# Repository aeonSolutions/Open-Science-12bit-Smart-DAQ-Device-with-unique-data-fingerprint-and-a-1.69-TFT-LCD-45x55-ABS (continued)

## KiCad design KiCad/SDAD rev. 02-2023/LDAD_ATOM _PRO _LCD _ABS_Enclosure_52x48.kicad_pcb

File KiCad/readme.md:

[PCB-Prototyping-Catalogue](https://github.com/aeonSolutions/PCB-Prototyping-Catalogue)  >>  [Laboratory Automation](https://github.com/aeonSolutions/PCB-Prototyping-Catalogue/tree/main/Laboratory%20Automation)  >>  [Smart DAQ](https://github.com/aeonSolutions/PCB-Prototyping-Catalogue/tree/main/Smart%20DAQ)  >> [12-bit Smart DAQs](https://github.com/aeonSolutions/PCB-Prototyping-Catalogue/tree/main/Smart%20DAQ/12-bit) >> 12-bit Smart DAQ Device with unique data fingerprint and a 1.69" TFT LCD  45x55 ABS

<div align="right">
 <a href="https://github-com.translate.goog/aeonSolutions/Open-Science-12bit-Smart-DAQ-Device-with-unique-data-fingerprint-and-a-1.69-TFT-LCD-45x55-ABS?_x_tr_sl=en&_x_tr_tl=pt&_x_tr_hl=en&_x_tr_pto=wapp">Change language</a>  <br>
Last change 13-04-2024
</div>

<br>

This folder contains the KiCad Project files, for the hardware electronics of the S.D.A.D.  Each KiCad project is available with a [creative commons share alike non-commercial license](https://creativecommons.org/licenses/by-nc-sa/4.0/deed.en) . 

<p align="center">
  <strong> <a href="https://aeonsolutions.github.io/portfolio/hardware_electronics/laboratory/">Interactive web view of the PCB Layout</a> </strong> <br>
 <sup>Click to view the latest revision of the PCB Layout</sup>
</p>

However, they're not fully complete. If you like it and are looking to use it on your projects, you can download the complete Kicad project files with a one-time donation, [click here](https://github.com/sponsors/aeonSolutions) to learn how,  and don't forget to include it in a message the name of the module/hardware electronics you need. <br> Thank you 🙏.

### Support all these open hardware projects and become a GitHub sponsor  
Did you like any of my PCB KiCad Designs? Help and Support my open work to all by becoming a GitHub sponsor.

<p align="center">

</p>

#

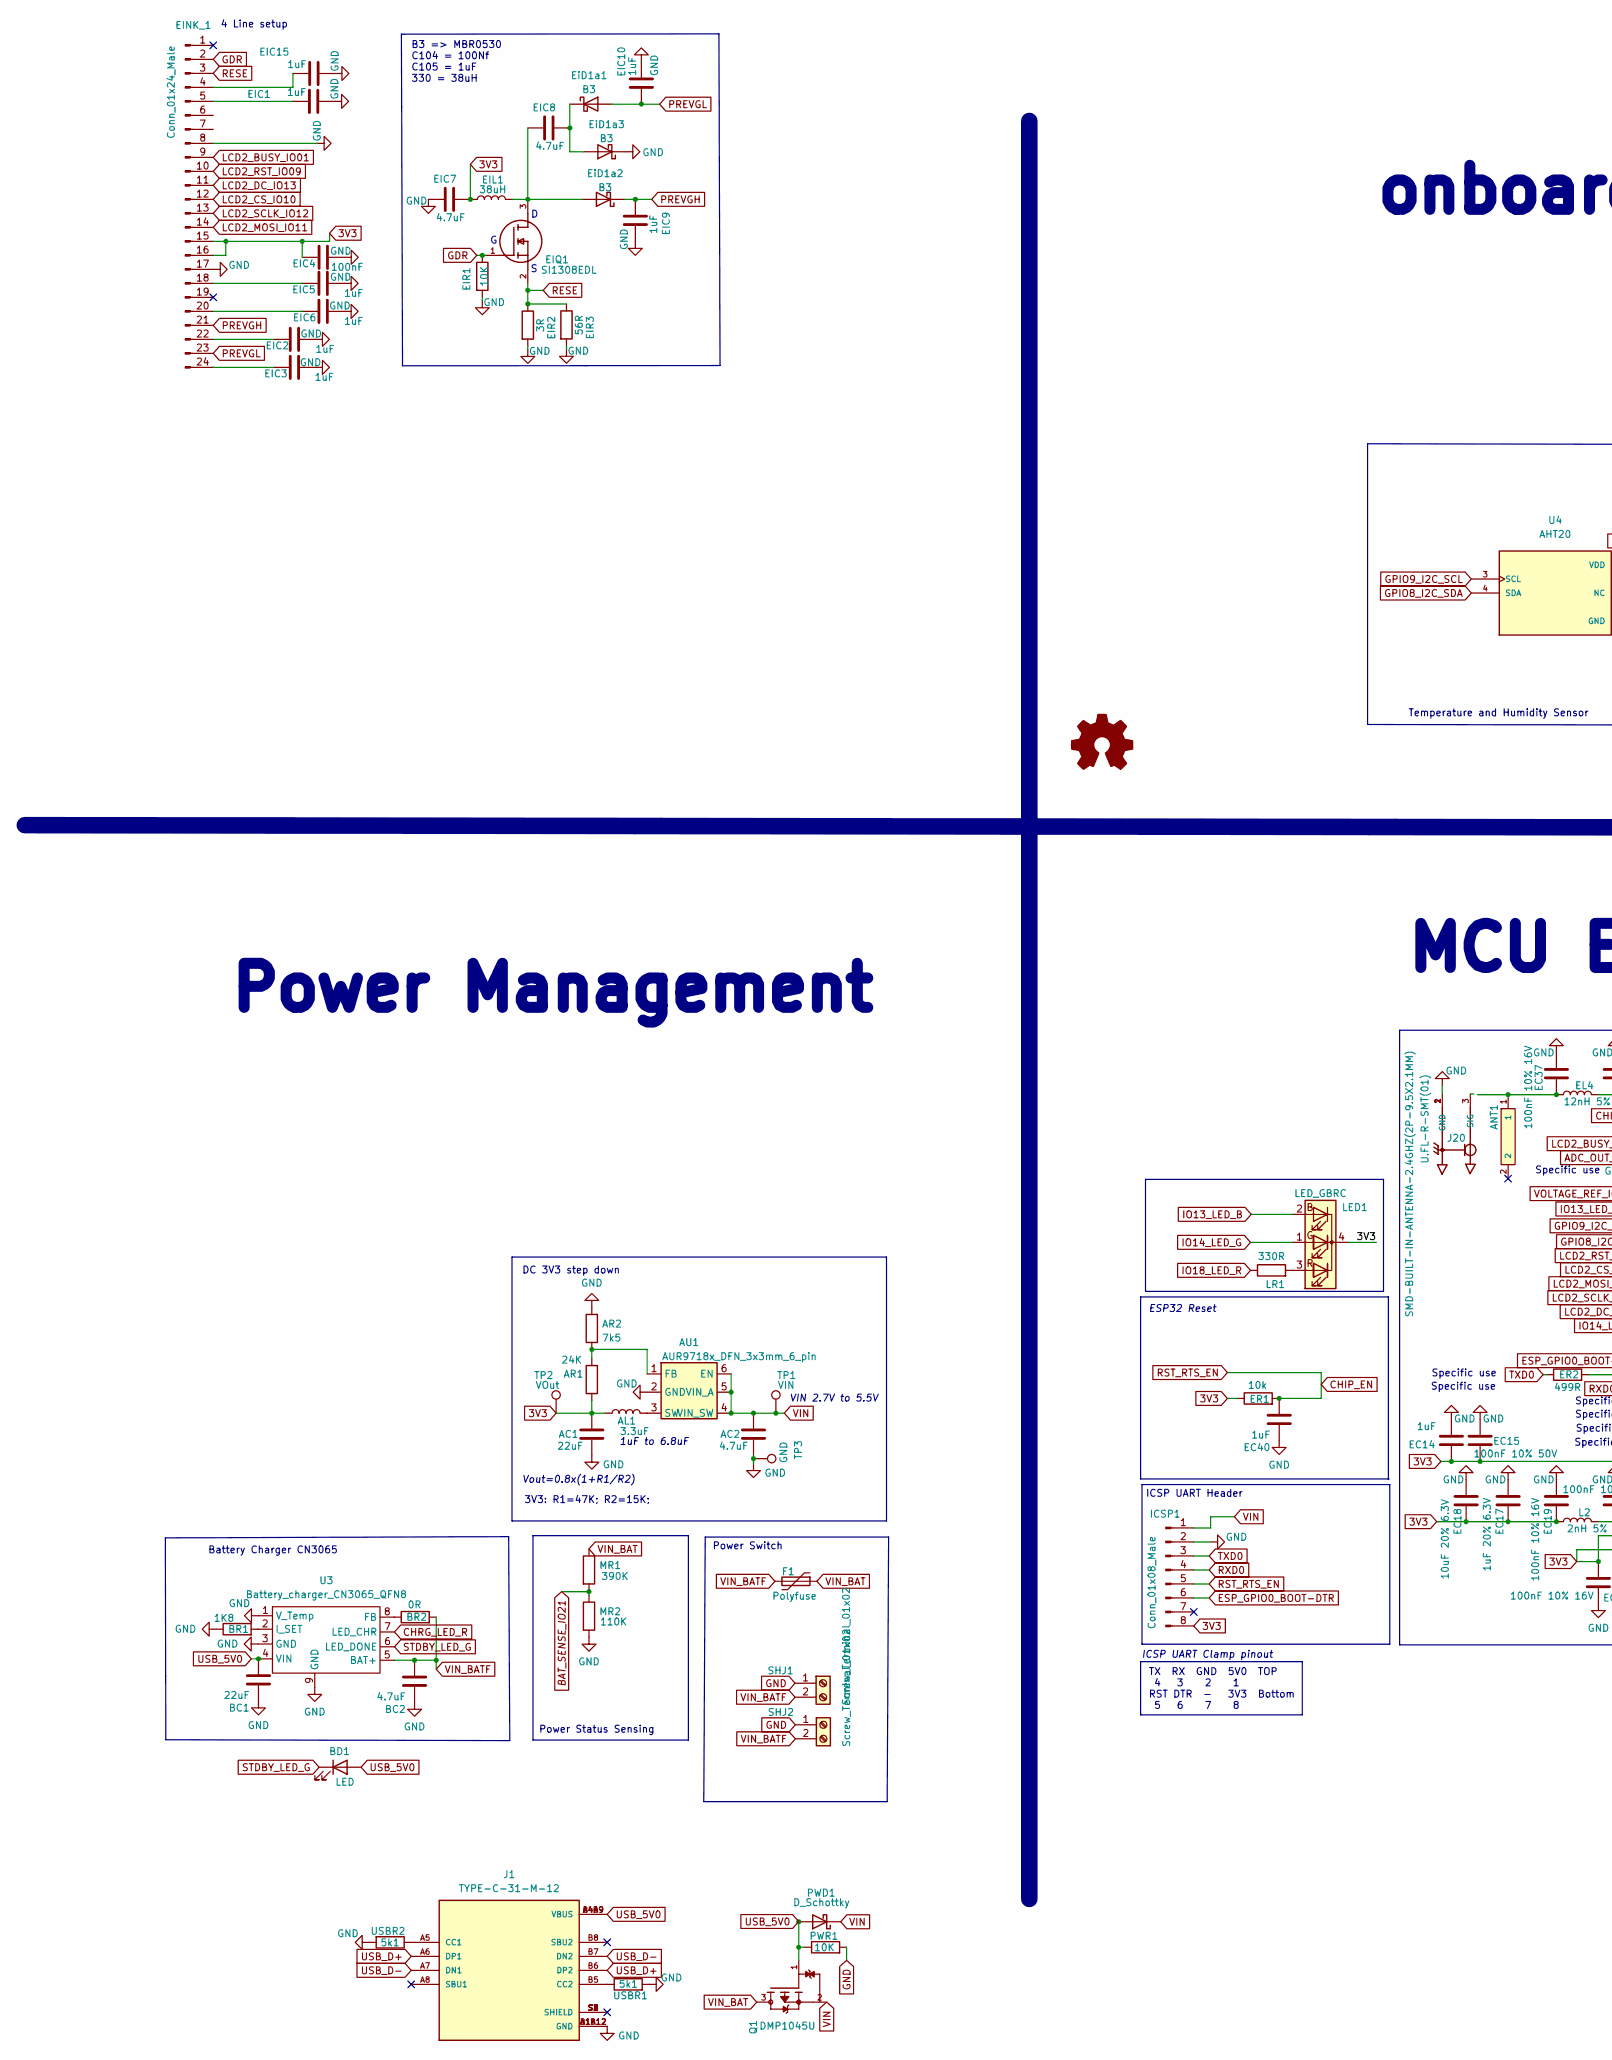
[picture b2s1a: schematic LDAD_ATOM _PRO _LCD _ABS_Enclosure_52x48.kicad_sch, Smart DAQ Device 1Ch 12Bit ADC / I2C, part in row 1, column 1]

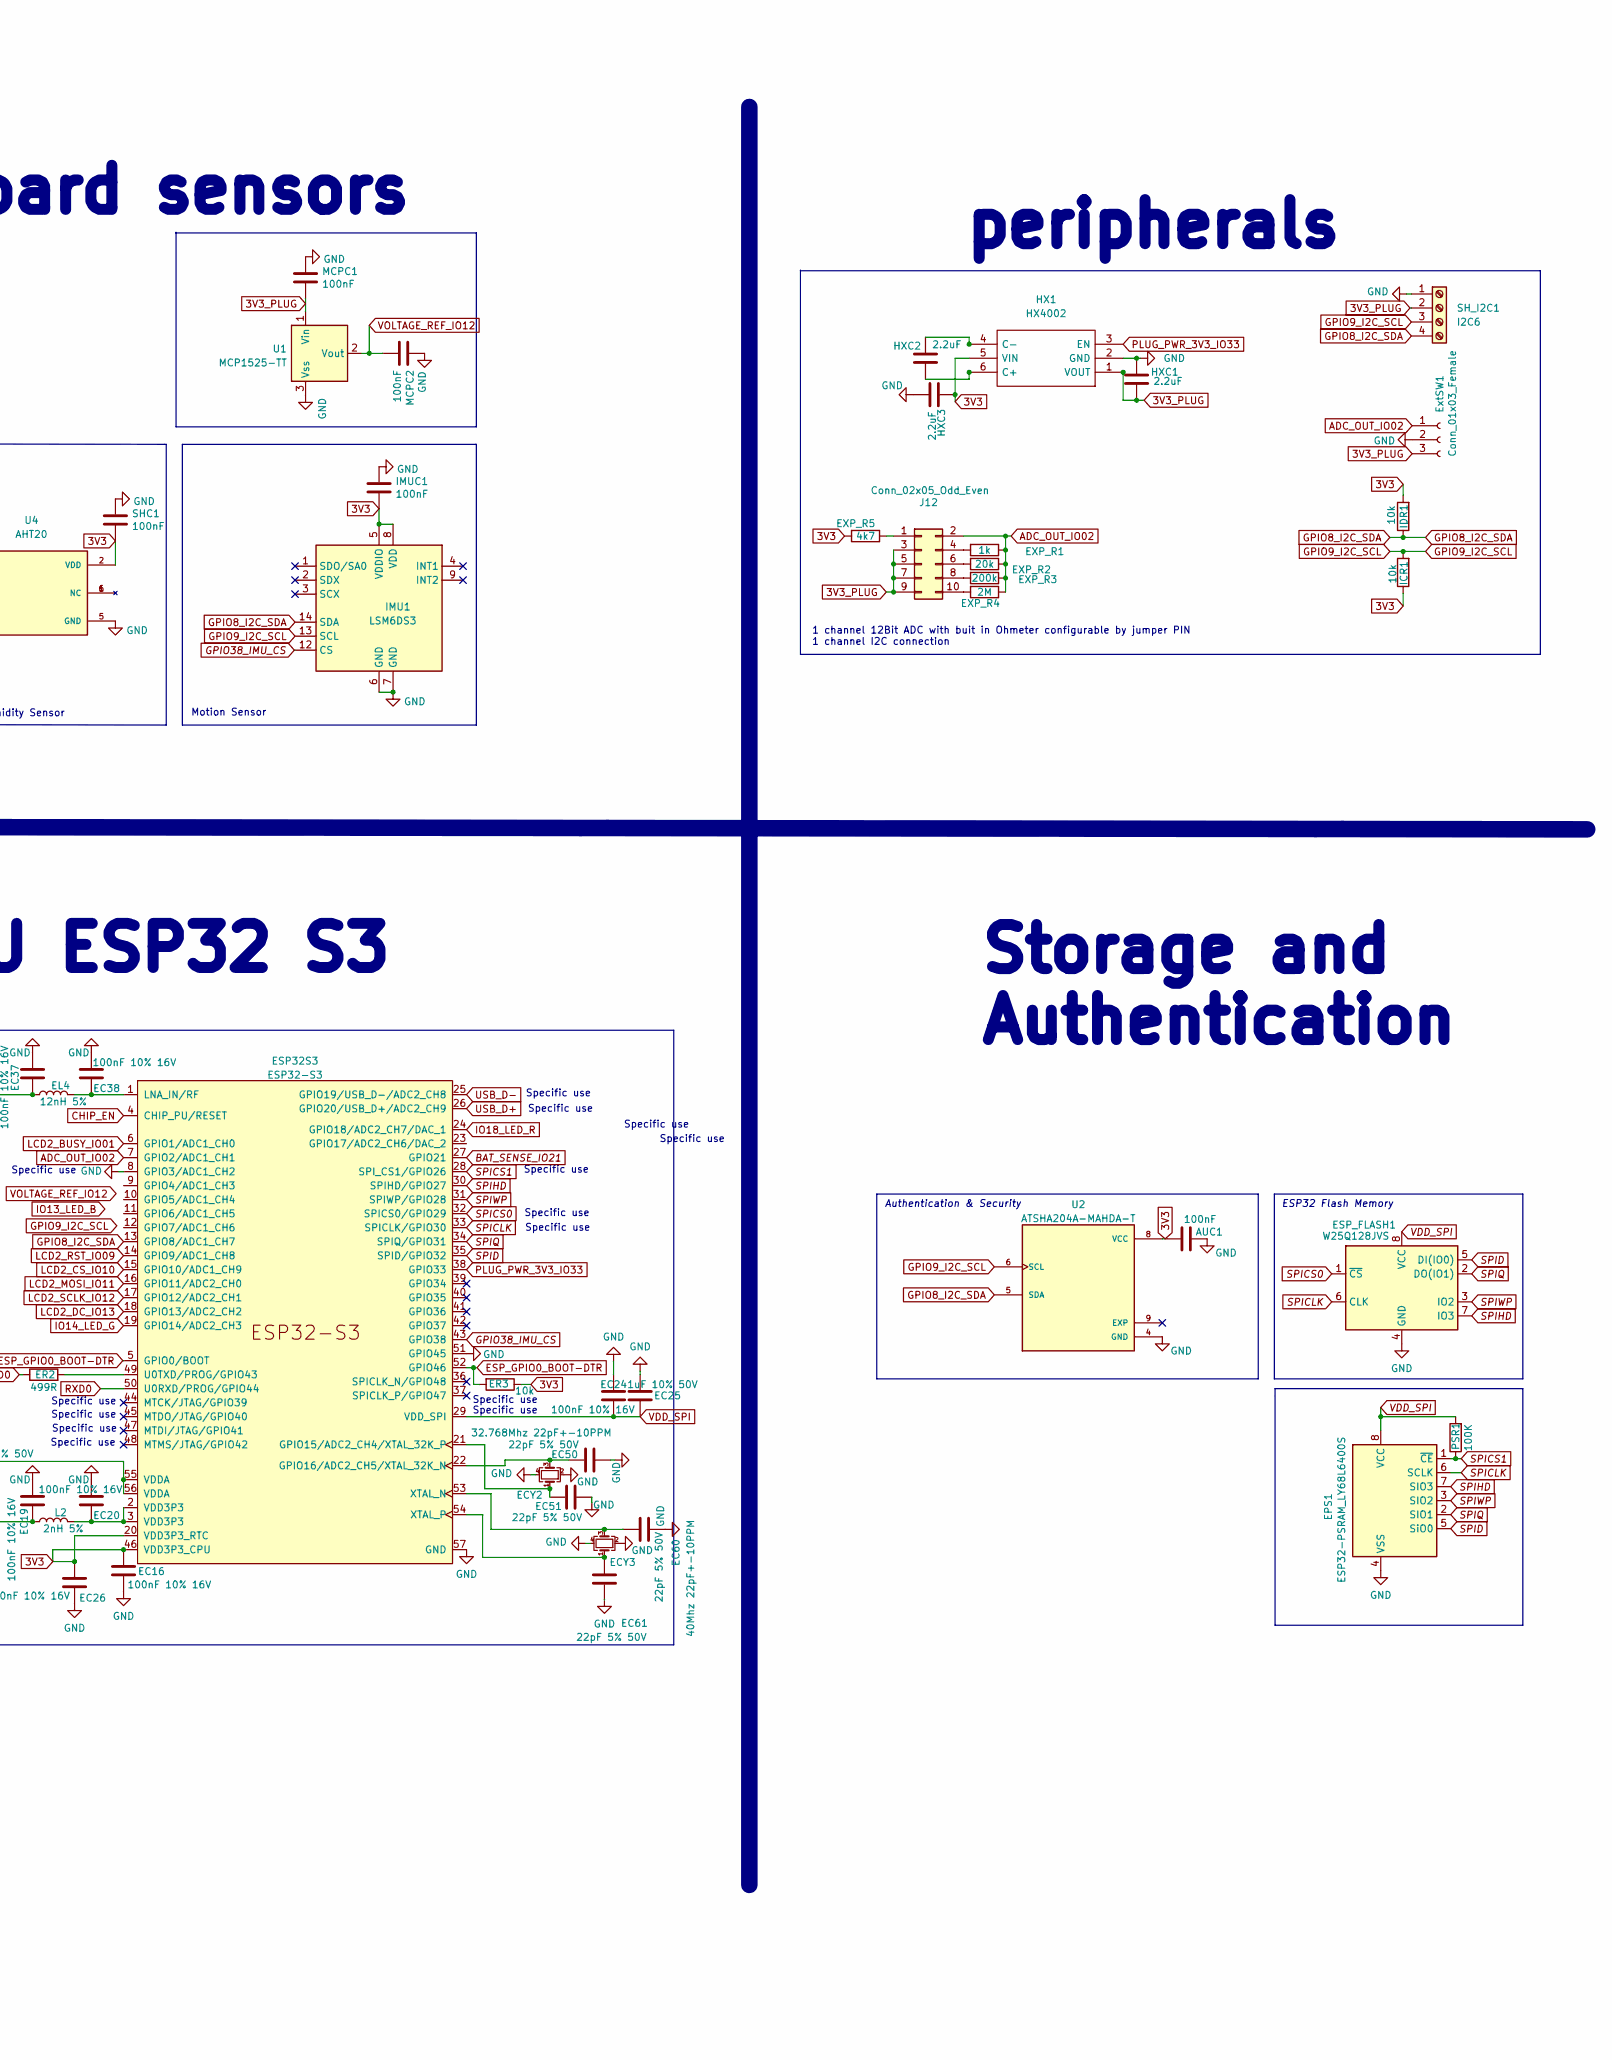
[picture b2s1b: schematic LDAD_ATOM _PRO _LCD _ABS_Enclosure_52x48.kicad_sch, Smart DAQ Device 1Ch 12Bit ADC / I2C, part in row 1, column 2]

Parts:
AC1: 22uF; C_0805_2012Metric_Pad1.18x1.45mm_HandSolder
AC2: 4.7uF; C_0805_2012Metric_Pad1.18x1.45mm_HandSolder
AL1: 3.3uF; L_1210_3225Metric
ANT1: SMD-BUILT-IN-ANTENNA-2.4GHZ(2P-9.5X2.1MM); AN9520_ANT2-SMD-9.5X2.1X1.0MM
AR1: 24K; R_0805_2012Metric_Pad1.20x1.40mm_HandSolder
AR2: 7k5; R_0805_2012Metric_Pad1.20x1.40mm_HandSolder
AU1: AUR9718x_DFN_3x3mm_6_pin; AUR9718 3x3mm 6 pin
AUC1: 100nF; C_0603_1608Metric
BC1: 22uF; C_0805_2012Metric
BC2: 4.7uF; C_0805_2012Metric
BD1: LED; LED_0805_2012Metric
BR1: 1K8; R_0603_1608Metric
BR2: 0R; R_0603_1608Metric
EC14: 1uF; C_0805_2012Metric
EC15: 100nF 10% 50V; C_0603_1608Metric
EC16, EC19, EC20, EC24, EC26, EC37, EC38: 100nF 10% 16V; C_0603_1608Metric
EC17: 1uF 20% 6.3V; C_0603_1608Metric
EC18: 10uF 20% 6.3V; C_0805_2012Metric
EC25: 1uF 10% 50V; C_0603_1608Metric
EC40: 1uF; C_0603_1608Metric
EC50, EC51, EC60, EC61: 22pF 5% 50V; C_0603_1608Metric
ECY2: 32.768Mhz 22pF+-10PPM; Crystal_SMD_EuroQuartz_MT-4Pin_3.2x2.5mm
ECY3: 40Mhz 22pF+-10PPM; Crystal_SMD_EuroQuartz_MT-4Pin_3.2x2.5mm
EIC1, EIC2, EIC3, EIC5, EIC6, EIC9, EIC10, EIC15: 1uF; C_0603_1608Metric
EIC4: 100nF; C_0603_1608Metric
EIC7, EIC8: 4.7uF; C_0603_1608Metric
EIL1: 38uH; L_0805_2012Metric
EINK_1: Conn_01x24_Male; 1.54 E-Ink 24 pin LDAD
EIQ1: SI1308EDL; SOT-323_SC-70; Mouser_Part_Number 78-SI1308EDL-T1-GE3
EIR1: 10K; R_0603_1608Metric
EIR2: 3R; R_0603_1608Metric
EIR3: 56R; R_0603_1608Metric
EL4: 12nH 5%; L_0805_2012Metric
EPS1: ESP32-PSRAM_LY68L6400S; SOIC-8_3.9x4.9mm_P1.27mm
ER1, ER3: 10k; R_0603_1608Metric
ER2: 499R; R_0603_1608Metric
ESP32S3: ESP32-S3; QFN-56-1EP_7x7mm_P0.4mm_EP5.6x5.6mm
ESP_FLASH1: W25Q128JVS; Flash SPI SON127P800X600X80-9N
EXP_R1: 1k; R_0603_1608Metric
EXP_R2: 20k; R_0603_1608Metric
EXP_R3: 200k; R_0603_1608Metric
EXP_R4: 2M; R_0603_1608Metric
EXP_R5: 4k7; R_0603_1608Metric
EiD1a1, EiD1a2, EiD1a3: B3; D_SOD-323
ExtSW1: Conn_01x03_Female; JST_SH_SM03B-SRSS-TB_1x03-1MP_P1.00mm_Horizontal
F1: Polyfuse; Fuse_1206_3216Metric_Pad1.42x1.75mm_HandSolder
HX1: HX4002; HX4002 SOT95 P280X125-6N; Manufacturer_Part_Number HX4002
HXC1, HXC2, HXC3: 2.2uF; C_0603_1608Metric
ICR1: 10k; R_0603_1608Metric
ICSP1: Conn_01x08_Male; SOIC_clipProgSmall
IDR1: 10k; R_0603_1608Metric
IMU1: LSM6DS3; LSM6DS3 PQFN50P300X250X86-14N
IMUC1: 100nF; C_0603_1608Metric
J1: TYPE-C-31-M-12; USB C HRO_TYPE-C-31-M-12; PARTREV A
J12: Conn_02x05_Odd_Even; Dip Switch 5 pin 1.27mm SW_DS05-127-2-06BK-SMT-TR
J20: U.FL-R-SMT(01); HRS_U.FL-R-SMT(01)
L2: 2nH 5%; L_0805_2012Metric
LED1: LED_GBRC; LED_1206_3210_RGB_Metric
LR1: 330R; R_0603_1608Metric
MCPC1, MCPC2: 100nF; C_0603_1608Metric
MR1: 390K; R_0805_2012Metric
MR2: 110K; R_0805_2012Metric
PSR1: 100K; R_0603_1608Metric
PWD1: D_Schottky; D_1206_3216Metric
PWR1: 10K; R_0805_2012Metric
Q1: DMP1045U; SOT-23; PARTREV 7 - 2
SHC1: 100nF; C_0603_1608Metric
SHJ1, SHJ2: Screw_Terminal_01x02; JST_SH_SM02B-SRSS-TB_1x02-1MP_P1.00mm_Horizontal
SH_I2C1: I2C6; JST_SH_SM04B-SRSS-TB_1x04-1MP_P1.00mm_Horizontal
TP1: VIN; TestPoint_Pad_D1.0mm
TP2: VOut; TestPoint_Pad_D1.0mm
TP3: GND; TestPoint_Pad_D1.0mm
U1: MCP1525-TT; SOT-23
U2: ATSHA204A-MAHDA-T; ATSHA204A Auth SOIC8; PART_REV A
U3: Battery_charger_CN3065_QFN8; QFN8 3.1x2.9mm QFNn-8 3x3 SON80P400X400X100-9N
U4: AHT20; AHT20 - PSON100P300X300X110-6N; PARTREV V1.0
USBR1, USBR2: 5k1; R_0603_1608Metric

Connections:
3V3: AC1.1, AL1.1, AR1.1, AUC1.2, EC14.2, EC15.2, EC16.1, EC17.1, EC18.1, EC19.1, EC26.1, EIC4.1, EIC7.1, EIL1.1, EINK_1.15, EINK_1.16, ER1.1, ER3.1, ESP32S3.20 (VDD3P3_RTC), ESP32S3.46 (VDD3P3_CPU), ESP32S3.55 (VDDA), ESP32S3.56 (VDDA), EXP_R5.2, HX1.5 (VIN), HXC3.2, ICR1.1, ICSP1.8, IDR1.2, IMU1.5 (VDDIO), IMU1.8 (VDD), IMUC1.2, L2.1, LED1.4 (K), SHC1.2, TP2.1, U2.8 (VCC), U4.2 (VDD); also elsewhere on the board
3V3_PLUG: ExtSW1.3, HX1.1 (VOUT), HXC1.1, J12.3, J12.5, J12.7, J12.9, MCPC1.2, SH_I2C1.2, U1.1 (Vin)
ADC_OUT_IO02: ESP32S3.7 (GPIO2/ADC1_CH1), EXP_R1.1, EXP_R2.1, EXP_R3.1, EXP_R4.1, ExtSW1.1, J12.2
BAT_SENSE_IO21: ESP32S3.27 (GPIO21), MR1.2, MR2.1
CHIP_EN: EC40.2, ER1.2, ESP32S3.4 (CHIP_PU/RESET), ICSP1.5
CHRG_LED_R: U3.7 (LED_CHR)
ESP_GPIO0_BOOT-DTR: ER3.2, ESP32S3.5 (GPIO0/BOOT), ESP32S3.52 (GPIO46), ICSP1.6
GDR: EINK_1.2, EIQ1.1, EIR1.1; also elsewhere on the board
GND: AC1.2, AC2.2, AR2.2, AU1.2 (GND), AUC1.1, BC1.1, BC2.1, BR1.1, EC14.1, EC15.1, EC16.2, EC17.2, EC18.2, EC19.2, EC20.2, EC24.2, EC25.2, EC26.2, EC37.2, EC38.2, EC40.1, EC50.2, EC51.2, EC60.2, EC61.2, ECY2.2, ECY2.4, ECY3.2, ECY3.4, EIC1.2, EIC2.2, EIC3.2, EIC4.2, EIC5.2, EIC6.2, EIC7.2, EIC9.2, EIC10.2, EIC15.2, EINK_1.8, EINK_1.17, EIR1.2, EIR2.2, EIR3.2, EPS1.4 (VSS), ESP32S3.8 (GPIO3/ADC1_CH2), ESP32S3.51 (GPIO45), ESP32S3.57 (GND), ESP_FLASH1.4 (GND), EiD1a3.1 (K), ExtSW1.2, HX1.2 (GND), HXC1.2, HXC3.1, ICSP1.2, IMU1.6 (GND), IMU1.7 (GND), IMUC1.1, J1.A1B12 (GND), J1.B1A12 (GND), J20.1 (GND), J20.2 (GND), MCPC1.1, MCPC2.1, MR2.2, PWR1.2, SHC1.1, SHJ1.1, SHJ2.1, SH_I2C1.1, TP3.1, U1.3 (Vss), U2.4 (GND), U3.1 (V_Temp), U3.3 (GND), U3.9 (GND), U4.5 (GND), USBR1.2, USBR2.2; also elsewhere on the board
GPIO8_I2C_SDA: ESP32S3.13 (GPIO8/ADC1_CH7), IDR1.1, IMU1.14 (SDA), SH_I2C1.4, U2.5 (SDA), U4.4 (SDA); also elsewhere on the board
GPIO9_I2C_SCL: ICR1.2, IMU1.13 (SCL), SH_I2C1.3, U2.6 (SCL), U4.3 (SCL); also elsewhere on the board
GPIO38_IMU_CS: ESP32S3.43 (GPIO38), IMU1.12 (CS)
IO13_LED_B: LED1.2 (BA)
IO14_LED_G: ESP32S3.19 (GPIO14/ADC2_CH3), LED1.1 (GA)
IO18_LED_R: ESP32S3.24 (GPIO18/ADC2_CH7/DAC_1), LR1.1
LCD2_BUSY_IO01: EINK_1.9, ESP32S3.6 (GPIO1/ADC1_CH0); also elsewhere on the board
LCD2_CS_IO10: EINK_1.12, ESP32S3.15 (GPIO10/ADC1_CH9); also elsewhere on the board
LCD2_DC_IO13: EINK_1.11, ESP32S3.18 (GPIO13/ADC2_CH2); also elsewhere on the board
LCD2_MOSI_IO11: EINK_1.14, ESP32S3.16 (GPIO11/ADC2_CH0); also elsewhere on the board
LCD2_RST_IO09: EINK_1.10, ESP32S3.14 (GPIO9/ADC1_CH8); also elsewhere on the board
LCD2_SCLK_IO12: EINK_1.13, ESP32S3.17 (GPIO12/ADC2_CH1); also elsewhere on the board
unnamed: ANT1.1, EC37.1, EL4.1
unnamed: AR1.2, AR2.1, AU1.1 (FB)
unnamed: AL1.2, AU1.3 (SW)
unnamed: EC20.1, ESP32S3.2 (VDD3P3), ESP32S3.3 (VDD3P3), L2.2
unnamed: EC51.1, ECY2.1, ESP32S3.21 (GPIO15/ADC2_CH4/XTAL_32K_P)
unnamed: EC50.1, ECY2.3, ESP32S3.22 (GPIO16/ADC2_CH5/XTAL_32K_N)
unnamed: EC38.1, EL4.2, ESP32S3.1 (LNA_IN/RF)
unnamed: ER2.2, ESP32S3.49 (U0TXD/PROG/GPIO43)
unnamed: EC60.1, ECY3.3, ESP32S3.53 (XTAL_N)
unnamed: EC61.1, ECY3.1, ESP32S3.54 (XTAL_P)
unnamed: EIC8.1, EiD1a1.1 (K), EiD1a3.2 (A)
unnamed: EIC8.2, EIL1.2, EIQ1.3, EiD1a2.2 (A)
unnamed: HX1.6 (C+), HXC2.1
unnamed: HX1.4 (C-), HXC2.2
unnamed: J1.A5 (CC1), USBR2.1
unnamed: J1.B5 (CC2), USBR1.1
unnamed 37: EIC15.1, EINK_1.4; also elsewhere on the board
unnamed 38: EIC1.1, EINK_1.5; also elsewhere on the board
unnamed 39: EIC5.1, EINK_1.18; also elsewhere on the board
unnamed 40: EIC6.1, EINK_1.20; also elsewhere on the board
unnamed 41: EIC2.1, EINK_1.22; also elsewhere on the board
unnamed 42: EIC3.1, EINK_1.24; also elsewhere on the board
unnamed: EXP_R5.1, J12.1
unnamed: EXP_R1.2, J12.4
unnamed: EXP_R2.2, J12.6
unnamed: EXP_R3.2, J12.8
unnamed: EXP_R4.2, J12.10
unnamed: LED1.3 (RA), LR1.2
unnamed: BR2.1, U3.8 (FB)
unnamed: BR1.2, U3.2 (I_SET)
PLUG_PWR_3V3_IO33: ESP32S3.38 (GPIO33), HX1.3 (EN)
PREVGH: EIC9.1, EINK_1.21, EiD1a2.1 (K); also elsewhere on the board
PREVGL: EIC10.1, EINK_1.23, EiD1a1.2 (A); also elsewhere on the board
RESE: EINK_1.3, EIQ1.2, EIR2.1, EIR3.1; also elsewhere on the board
RXD0: ESP32S3.50 (U0RXD/PROG/GPIO44), ICSP1.4
SPICLK: EPS1.6 (SCLK), ESP32S3.33 (SPICLK/GPIO30), ESP_FLASH1.6 (CLK)
SPICS0: ESP32S3.32 (SPICS0/GPIO29), ESP_FLASH1.1 (~CS)
SPICS1: EPS1.1 (~CE), ESP32S3.28 (SPI_CS1/GPIO26), PSR1.1
SPID: EPS1.5 (SiO0), ESP32S3.35 (SPID/GPIO32), ESP_FLASH1.5 (DI(IO0))
SPIHD: EPS1.7 (SIO3), ESP32S3.30 (SPIHD/GPIO27), ESP_FLASH1.7 (IO3)
SPIQ: EPS1.2 (SIO1), ESP32S3.34 (SPIQ/GPIO31), ESP_FLASH1.2 (DO(IO1))
SPIWP: EPS1.3 (SIO2), ESP32S3.31 (SPIWP/GPIO28), ESP_FLASH1.3 (IO2)
STDBY_LED_G: BD1.1 (K), U3.6 (LED_DONE)
TXD0: ER2.1, ICSP1.3
USB_5V0: BC1.2, BD1.2 (A), J1.A4B9 (VBUS), J1.B4A9 (VBUS), PWD1.2 (A), PWR1.1, Q1.1, U3.4 (VIN)
USB_D+: ESP32S3.26 (GPIO20/USB_D+/ADC2_CH9), J1.A6 (DP1), J1.B6 (DP2)
USB_D-: ESP32S3.25 (GPIO19/USB_D-/ADC2_CH8), J1.A7 (DN1), J1.B7 (DN2)
VDD_SPI: EC24.1, EC25.1, EPS1.8 (VCC), ESP32S3.29 (VDD_SPI), ESP_FLASH1.8 (VCC), PSR1.2
VIN: AC2.1, AU1.4 (VIN_SW), AU1.5 (VIN_A), AU1.6 (EN), ICSP1.1, PWD1.1 (K), Q1.2, TP1.1
VIN_BAT: F1.1, MR1.1, Q1.3
VIN_BATF: BC2.2, BR2.2, F1.2, SHJ1.2, SHJ2.2, U3.5 (BAT+)
VOLTAGE_REF_IO12: MCPC2.2, U1.2 (Vout)

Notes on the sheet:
Specific use
3V3: R1=47K; R2=15K;
ICSP UART Header
peripherals
Vout=0.8x(1+R1/R2)
ESP32 Flash Memory
DC 3V3 step down
ESP32 Reset
Temperature and Humidity Sensor
4 Line setup
1uF to 6.8uF
Motion Sensor
1 channel 12Bit ADC with buit in Ohmeter configurable by jumper PIN 1 channel I2C connection
onboard sensors
ICSP UART Clamp pinout
Storage and Authentication
Battery Charger CN3065
Power Management
Authentication & Security
VIN 2.7V to 5.5V
Power Switch
MCU ESP32 S3
TX RX GND 5V0 TOP 4 3 2 1 RST DTR - 3V3 Bottom 5 6 7 8
B3 => MBR0530 C104 = 100Nf C105 = 1uF 330 = 38uH
Power Status Sensing

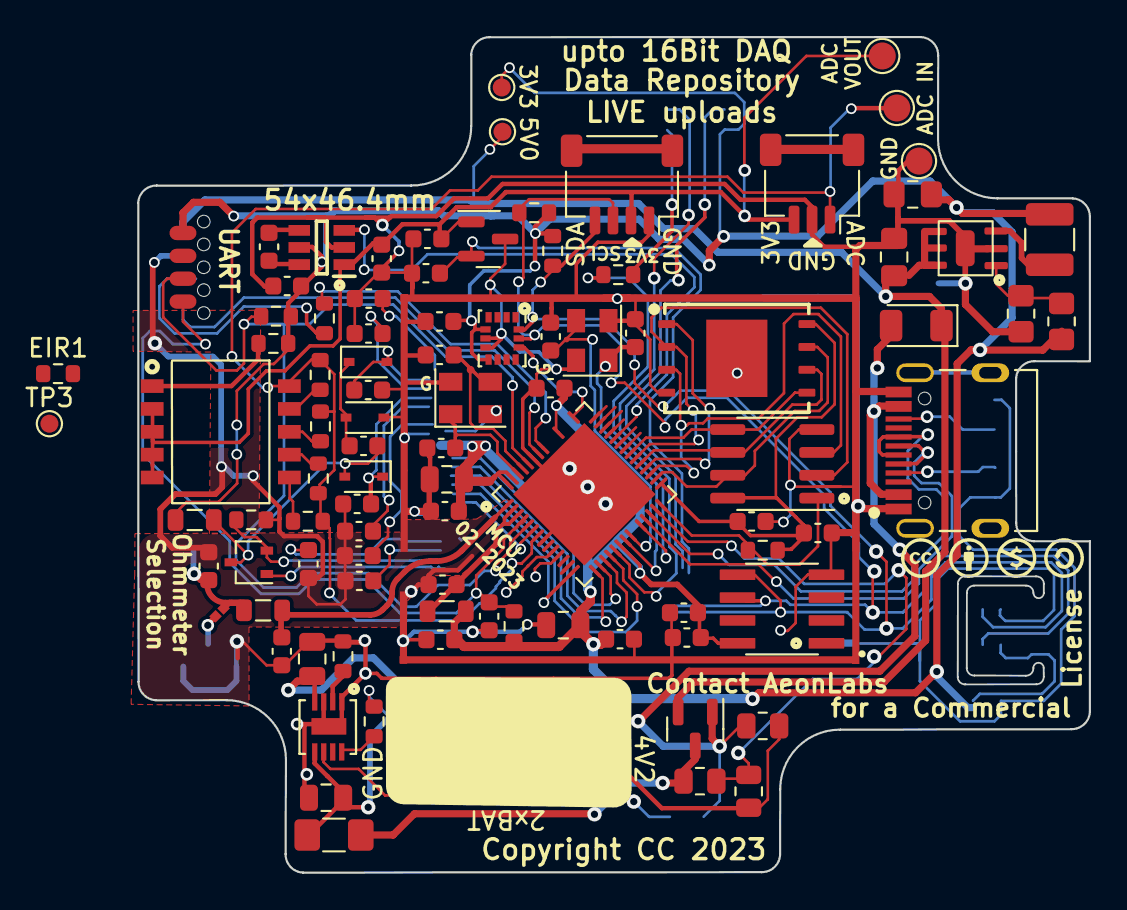
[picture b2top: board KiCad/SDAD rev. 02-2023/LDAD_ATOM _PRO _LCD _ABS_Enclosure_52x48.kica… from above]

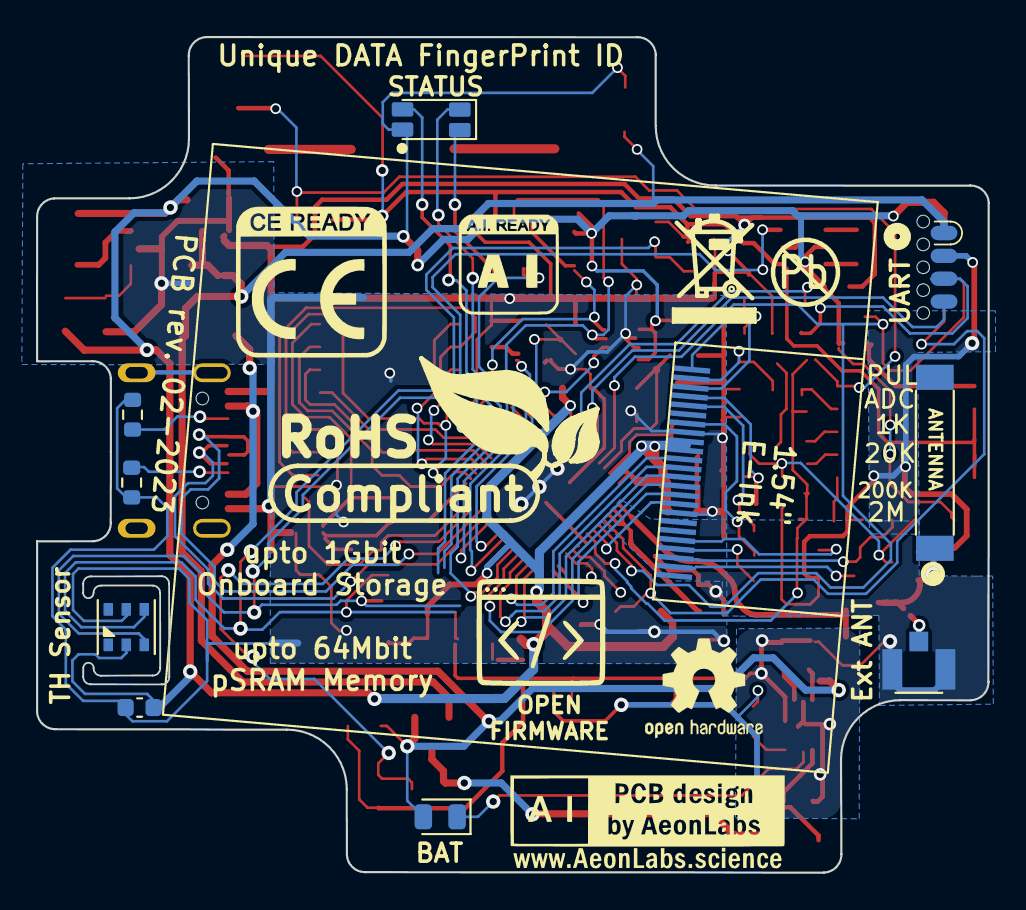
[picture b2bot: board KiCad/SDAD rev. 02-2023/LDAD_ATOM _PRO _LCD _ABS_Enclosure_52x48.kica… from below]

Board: 2 copper layers, 52.9 x 46.4 mm, 102 parts (13 on the bottom side), 71 nets.

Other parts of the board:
J2: Conn_01x24_Male; 1.54 E-Ink 24 pin LDAD
Sign-PbFree: LOGO_PBFREE
Sign-RecycleBin: LOGO_RECYCLEBIN_1
Sign-RoHS: LOGO_ROHS_1

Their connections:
3V3: J2.15, J2.16; also elsewhere on the board
GDR: J2.2; also elsewhere on the board
GND: J2.8, J2.17; also elsewhere on the board
GPIO8_I2C_SDA: J2.7; also elsewhere on the board
GPIO9_I2C_SCL: J2.6; also elsewhere on the board
LCD2_BUSY_IO01: J2.9; also elsewhere on the board
LCD2_CS_IO10: J2.12; also elsewhere on the board
LCD2_DC_IO13: J2.11; also elsewhere on the board
LCD2_MOSI_IO11: J2.14; also elsewhere on the board
LCD2_RST_IO09: J2.10; also elsewhere on the board
LCD2_SCLK_IO12: J2.13; also elsewhere on the board
unnamed 37: J2.4; also elsewhere on the board
unnamed 38: J2.5; also elsewhere on the board
unnamed 39: J2.18; also elsewhere on the board
unnamed 40: J2.20; also elsewhere on the board
unnamed 41: J2.22; also elsewhere on the board
unnamed 42: J2.24; also elsewhere on the board
PREVGH: J2.21; also elsewhere on the board
PREVGL: J2.23; also elsewhere on the board
RESE: J2.3; also elsewhere on the board
